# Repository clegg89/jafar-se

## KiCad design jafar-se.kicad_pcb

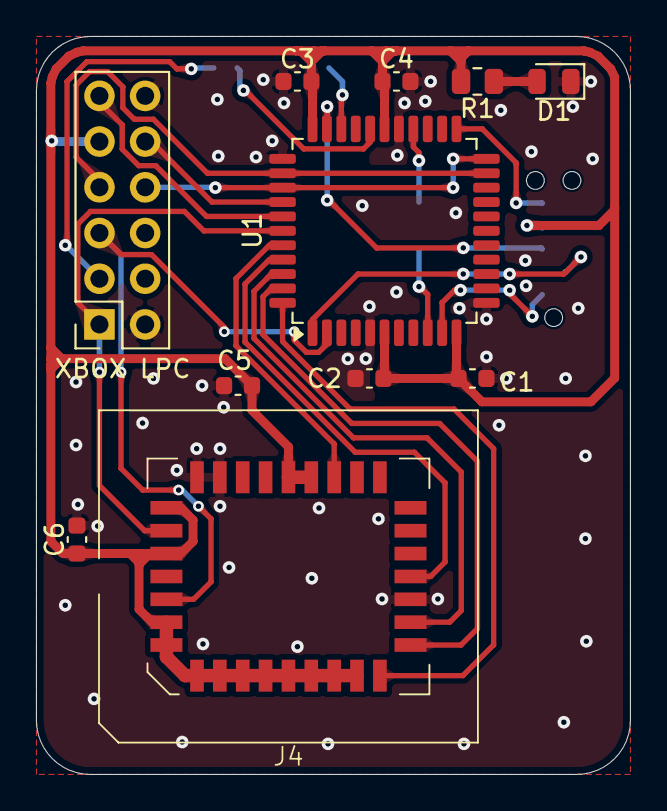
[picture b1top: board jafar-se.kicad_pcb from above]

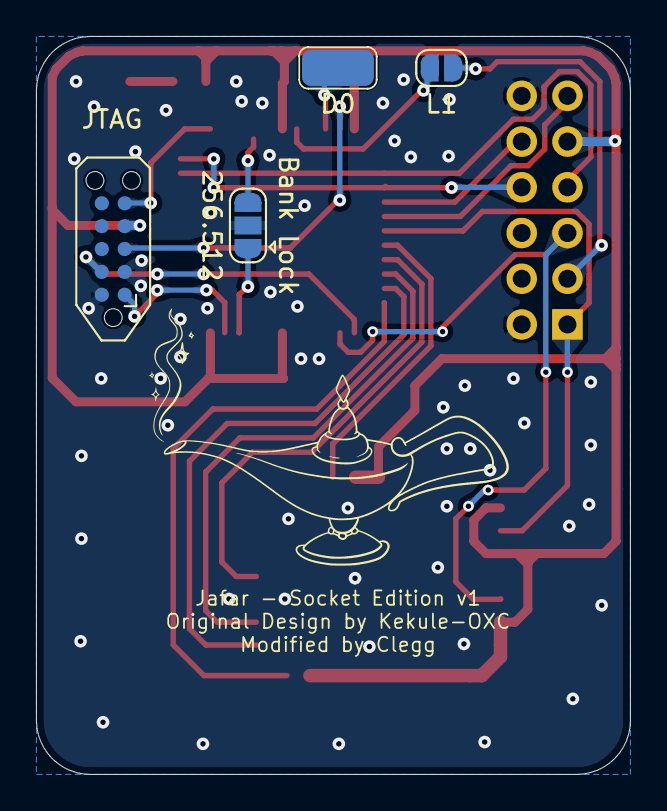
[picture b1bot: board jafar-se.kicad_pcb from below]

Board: 2 copper layers, 33.0 x 41.0 mm, 15 parts (4 on the bottom side), 23 nets.

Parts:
C1, C2, C3, C4, C5, C6: 100nF; C_0603_1608Metric
D1: LED; LED_0805_2012Metric
J1: XBOX LPC; PinSocket_2x06_P2.54mm_Vertical
J2: JTAG; Tag-Connect_TC2050-IDC-NL_2x05_P1.27mm_Vertical
J3: D0; SolderWirePad_1x01_SMD_2x4mm
J4: PLCC-32 Socket; PLCC-32_SMD-Socket
JP1: Bank Lock; SolderJumper-3_P1.3mm_Open_RoundedPad1.0x1.5mm
JP2: L1; SolderJumper-2_P1.3mm_Open_RoundedPad1.0x1.5mm
R1: 1k; R_0805_2012Metric
U1: LC4032V-75TN44I; TQFP-44_10x10mm_P0.8mm

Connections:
+3V3: C1.1, C2.1, C3.1, C4.1, C5.1, C6.1, J1.9, J2.4, J4.3, J4.4, J4.5, J4.6, J4.7, J4.8, J4.9, J4.10, J4.11, J4.12, J4.24, J4.25, J4.30, J4.32, R1.1, U1.6 (VCCO_0), U1.11 (VCC), U1.28 (VCCO_1), U1.33 (VCC)
/BT: JP1.3 (B), U1.26 (B7)
/D0: J3.1 (Pin_1_1), U1.31 (B10)
/FLAD0: J4.13, U1.44 (A4)
/FLAD1: J4.14, U1.43 (A3)
/FLAD2: J4.15, U1.42 (A2)
/FLAD3: J4.17, U1.41 (A1)
/H0: JP1.1 (A), U1.9 (A10)
/LED: D1.2 (A), R1.2
/TCK: J2.1, U1.10 (TCK)
/TDI: J2.9, U1.1 (TDI)
/TDO: J2.3, U1.32 (TDO)
/TMS: J2.5, U1.23 (TMS)
/XLAD0: J1.11, U1.38 (B15/GOE1)
/XLAD1: J1.10, U1.37 (B14)
/XLAD2: J1.8, U1.22 (B4), U1.36 (B13)
/XLAD3: J1.7, U1.21 (B3), U1.35 (B12)
/XLCLK: J1.1, J4.31, U1.39 (CLK0/I)
/XLFRAME_L1: JP2.2 (B), U1.29 (B8)
/~FLFRAME: J4.23, U1.40 (A0/GOE0)
/~XLFRAME: J1.3, JP2.1 (A)
/~XLRESET: J1.5, J4.2, U1.2 (A5)
GND: C1.2, C2.2, C3.2, C4.2, C5.2, C6.2, D1.1 (K), J1.2, J1.12, J2.2, J2.10, J4.16, J4.28, J4.29, JP1.2 (C), U1.5 (GND_0), U1.12 (GND), U1.27 (GND_1), U1.34 (GND)

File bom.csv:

"#","Reference","Qty","Value","Description","Distributor Link 1","Distributor Link 2","LCSC"
"1","C1,C2,C3,C4,C5,C6","6","100nF","Bypass Capacitor","https://www.digikey.com/en/products/detail/samsung-electro-m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","https://www.mouser.com/en/ProductDetail/Samsung-Electro-Mech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","C913912"
"2","D1","1","LED","Power Status LED","https://www.digikey.com/en/products/detail/liteon/LTST-C171G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","https://www.mouser.com/en/ProductDetail/LITEON/LTST-C171GKT?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","C913075"
"3","J1","1","XBOX LPC","Xbox LPC Header","https://www.digikey.com/en/products/detail/te-connectivity-a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","https://www.mouser.com/en/ProductDetail/TE-Connectivity/5-53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","C18078145"
"4","R1","1","1k","RES 1kΩ ±1% 125mW 0805","https://www.digikey.com/en/products/detail/yageo/RC0805FR-07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","https://www.mouser.com/en/ProductDetail/YAGEO/RC0805FR-071KL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","C95781"
"5","U1","1","LC4032V-75TN44I","32 Macrocell CPLD","https://www.digikey.com/en/products/detail/lattice-semicondu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","https://www.mouser.com/en/ProductDetail/Lattice/LC4032V-75TN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","C1521114"
"6","U2","1","SST49LF080A-33-4C-NHE","8Mbit LPC Flash PLCC-32","https://www.digikey.com/en/products/detail/microchip-technol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","https://www.mouser.com/en/ProductDetail/Microchip-Technology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","C645941"
